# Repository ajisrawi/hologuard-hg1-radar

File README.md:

# HoloGuard HG-1: Ku-band GaN 4D holographic counter-UAS radar

A staring (holographic) 6 TX × 48 RX MIMO radar in the **same 163 × 203 × 57 mm envelope as the Echodyne EchoGuard**. It's lighter (1.06 kg vs 1.25 kg), uses less power (46.8 W vs 50 W), has longer range (Phantom 4: 1.5 km detect / 2.3 km spotlight track vs > 1 km) and better 3D accuracy (0.2° / 0.35° at 1 km vs 1° / 1.5°). Every beam is formed digitally from a 288-element virtual array, every CPI.

| Step | Documents | Sources / outputs |
|---|---|---|
| 1. High-level design | [docs/01_System_Design.md](docs/01_System_Design.md) | `hg1_params.py` (single source of truth), `analysis/` (link budget, trade study, figures) |
| 2. Board design + schematics | [docs/03_Board_Design.md](docs/03_Board_Design.md), [docs/05_Schematics.md](docs/05_Schematics.md) | `board/schematic/generate_schematics.py` → `board/kicad/*.kicad_sch` (ERC 0/0, parity clean); `board/generate_boards.py` → `*.kicad_pcb` (0 DRC errors), renders, `BOM_HG1.csv` |
| 3. Antenna design | [docs/02_Antenna.md](docs/02_Antenna.md), [docs/06_EM_Simulation.md](docs/06_EM_Simulation.md) | `antenna/array_design.py` → element CSV/JSON, beam patterns; `antenna/em/` → full-wave FEM (EMerge) of the element, scan-optimised on Modal |
| 4. Enclosure (FreeCAD) | [docs/04_Mechanical.md](docs/04_Mechanical.md) | `mech/build_enclosure.py` → `mech/out/HG1_enclosure.FCStd / .step / *.stl` |
| 5. Render (Blender) | [docs/04_Mechanical.md](docs/04_Mechanical.md) | `mech/render_blender.py` → `render/*.png`, `HG1_scene.blend` |
| 6. Firmware | [firmware/README.md](firmware/README.md) | Versal DSP chain + tracker (C++), STM32 housekeeping (C), simulator + verification |

## Regenerate everything

```bash
python analysis/system_budget.py
```

```bash
python antenna/array_design.py
```

```bash
"C:/Program Files/KiCad/10.0/bin/python.exe" board/generate_boards.py
```

```bash
sh board/render_boards.sh
```

```bash
"C:/Program Files/FreeCAD 1.1/bin/freecadcmd.exe" mech/build_enclosure.py
```

```bash
"C:/Program Files/Blender Foundation/Blender 5.2/blender.exe" -b --factory-startup -P mech/render_blender.py
```

```bash
cmd //c firmware\\build_host.bat
```

```bash
python firmware/sim/gen_scenario.py && firmware/build/hg1_radard.exe --input firmware/sim/out/scenario.iq --out firmware/sim/out && python firmware/sim/verify.py
```

## Honest status

This is a complete **design-stage** package:

- **Computed:** link budget, array and patterns.
- **Full-wave simulated:**
  - The radiating element has been simulated and optimised in an infinite-array FEM model to 60° azimuth / 40° elevation scan.
  - Its active |S11| is below −10 dB over 0.52–0.70 GHz around 16 GHz at every scan angle; see docs/06.
- **Schematics:** complete for all three boards, with ERC 0/0 and schematic↔PCB parity clean.
- **DRC-clean but unfinished:** board layouts are placed and RF-routed; the remaining digital/power routing is still to do.
- **Modelled:** enclosure and renders.
- **Verified in simulation:** the firmware, against independently synthesised raw ADC data.

Before hardware, it still needs:

- a finite-array and radome EM check, plus an independent-solver cross-check;
- the custom HRX-8 receiver RFIC (or a COTS brassboard);
- confirmation of Ku GaN PA availability;
- thermal CFD;
- the AIE/PL kernel implementation on the Versal.

Open risks are listed in docs/01 §10.

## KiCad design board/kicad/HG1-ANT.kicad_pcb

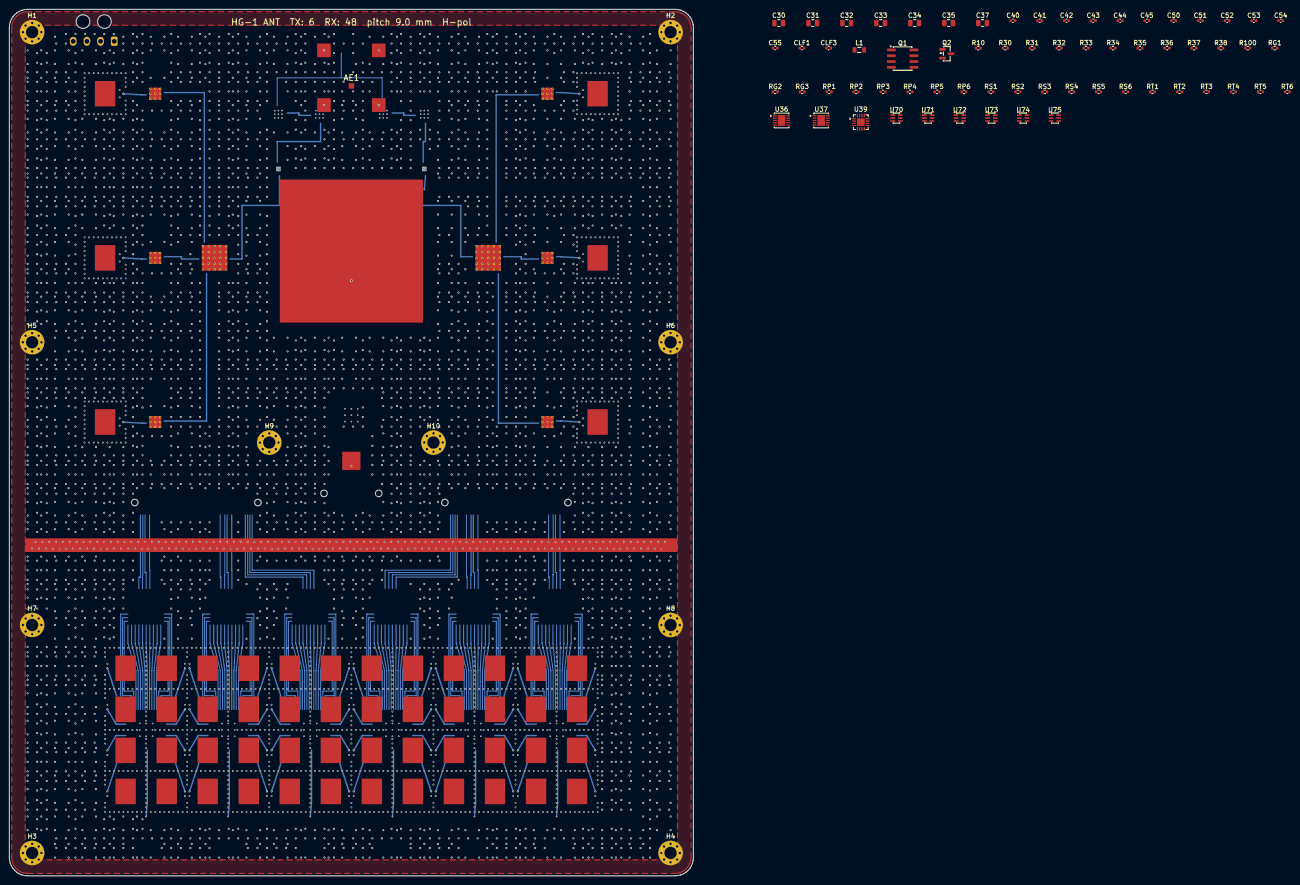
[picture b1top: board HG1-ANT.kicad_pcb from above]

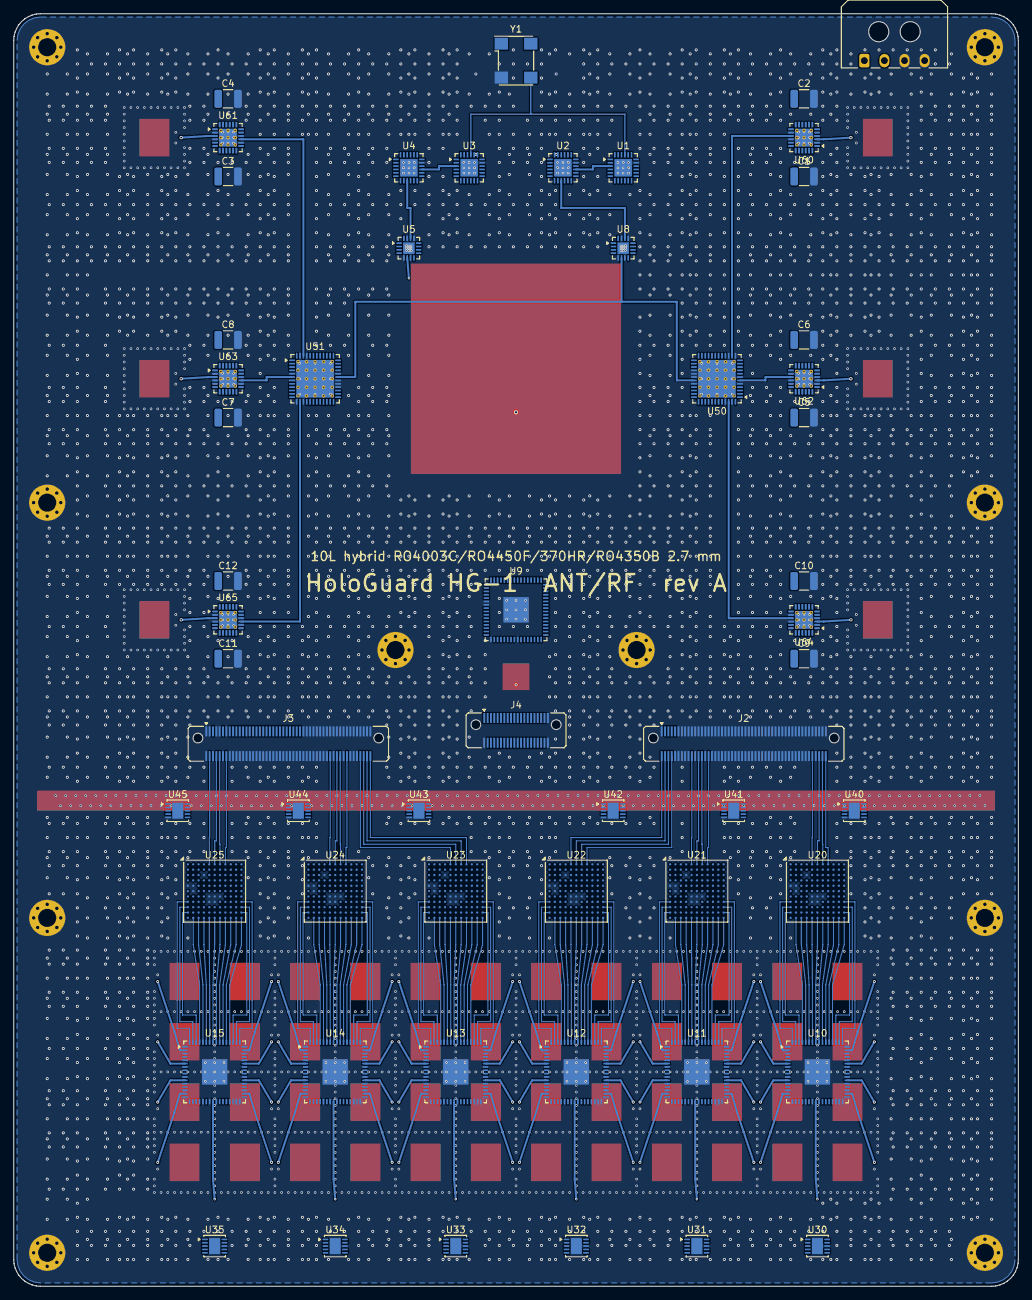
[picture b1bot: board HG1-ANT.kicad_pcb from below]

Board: 10 copper layers, 150.0 x 190.0 mm, 132 parts (56 on the bottom side), 251 nets.

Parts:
AE1: GNSS L1/L5 patch; GNSS_PATCH_18x18
C1, C2, C3, C4, C5, C6, C7, C8, C9, C10, C11, C12: 10u 50V; C_1210_3225Metric
C30, C31, C32, C33, C34, C35: 10u; C_0805_2012Metric
C37: 47u; C_0805_2012Metric
C40, C41, C42, C43, C44, C45: 1u; C_0402_1005Metric
C50, C51, C52, C53, C54, C55: 100n; C_0402_1005Metric
CLF1, CLF3: 2.2n C0G loop filter; C_0402_1005Metric
H1, H2, H3, H4, H5, H6, H7, H8, H9, H10: M2.5; MountingHole_2.7mm_M2.5_Pad_Via
J1: Micro-Fit 4p power in; Molex_Micro-Fit_3.0_43650-0400_1x04_P3.00mm_Horizontal
J2, J3: LSHM-150 JESD mezzanine; Samtec_LSHM-150-xx.x-x-DV-N_2x50_P0.50mm_Vertical
J4: LSHM-120 control mezzanine; Samtec_LSHM-120-xx.x-x-DV-N_2x20_P0.50mm_Vertical
L1: 1u; L_0805_2012Metric
Q1: P-MOSFET -60 V drain switch; SOIC-8_3.9x4.9mm_P1.27mm
Q2: 2N7002; SOT-23
R10, R100: 5.1k; R_0402_1005Metric
R30, R31, R32, R33, R34, R35, R36: 33.2k 0.1%; R_0402_1005Metric
R37: 20k; R_0402_1005Metric
R38: 80.6k; R_0402_1005Metric
RG1, RG2: 10k; R_0402_1005Metric
RG3: 100k; R_0402_1005Metric
RP1, RP2, RP3, RP4, RP5, RP6: 10k 0.1%; R_0402_1005Metric
RS1, RS2, RS3, RS4, RS5, RS6: 10m 1% 0805; R_0402_1005Metric
RT1, RT2, RT3, RT4, RT5, RT6: 10k B3435; R_0402_1005Metric
U1, U3: ADF4159; QFN-24-1EP_4x4mm_P0.5mm_EP2.6x2.6mm
U2, U4: HMC733LC4B; QFN-24-1EP_4x4mm_P0.5mm_EP2.6x2.6mm
U5, U8: HMC903LP3E; QFN-16-1EP_3x3mm_P0.5mm_EP1.7x1.7mm
U9: HMC7044; QFN-64-1EP_9x9mm_P0.5mm_EP3.8x3.8mm
U10, U11, U12, U13, U14, U15: HRX-8; QFN-64-1EP_9x9mm_P0.5mm_EP3.8x3.8mm
U20, U21, U22, U23, U24, U25: AD9083BBCZ; BGA-121_9.0x9.0mm_Layout11x11_P0.8mm_Ball0.4mm_Pad0.35mm_NS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
U30, U31, U32, U33, U34, U35: LT3045 3.3 V; DFN-10-1EP_3x3mm_P0.5mm_EP1.65x2.38mm
U36: LT3045 3.3 V (RF); DFN-10-1EP_3x3mm_P0.5mm_EP1.65x2.38mm
U37: TPS62913 1.0 V; DFN-10-1EP_3x3mm_P0.5mm_EP1.65x2.38mm
U39: ADS7138; QFN-16-1EP_3x3mm_P0.5mm_EP1.7x1.7mm
U40, U41, U42, U43, U44, U45: ADP7159 1.8 V; DFN-10-1EP_3x3mm_P0.5mm_EP1.65x2.38mm
U50, U51: ADAR1000; QFN-48-1EP_7x7mm_P0.5mm_EP5.6x5.6mm_ThermalVias
U60, U61, U62, U63, U64, U65: GaN PA 1 W; QFN-24-1EP_4x4mm_P0.5mm_EP2.65x2.65mm_ThermalVias
U70, U71, U72, U73, U74, U75: INA186A3; SOT-363_SC-70-6
Y1: 100 MHz OCXO; Oscillator_SMD_Diodes_FN-4Pin_7.0x5.0mm

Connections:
+1V0_ADC: C37.1, L1.2, R37.1, U20.E5, U20.E6, U20.E7, U21.E5, U21.E6, U21.E7, U22.E5, U22.E6, U22.E7, U23.E5, U23.E6, U23.E7, U24.E5, U24.E6, U24.E7, U25.E5, U25.E6, U25.E7
+3V3_RF: RP1.1, RP2.1, RP3.1, RP4.1, RP5.1, RP6.1, U1.5, U1.6, U1.7, U1.8, U1.16, U3.5, U3.6, U3.7, U3.8, U3.16, U5.3, U8.3, U9.10, U9.11, U9.12, U9.13, U36.9, U36.10, U39.14, U40.1, U40.2, U40.3, U41.1, U41.2, U41.3, U42.1, U42.2, U42.3, U43.1, U43.2, U43.3, U44.1, U44.2, U44.3, U45.1, U45.2, U45.3, U50.10, U50.11, U50.21, U51.10, U51.11, U51.21, U70.1, U71.1, U72.1, U73.1, U74.1, U75.1, Y1.1, Y1.4
+5V: J1.2, U2.3, U2.4, U4.3, U4.4, U30.1, U30.2, U30.3, U31.1, U31.2, U31.3, U32.1, U32.2, U32.3, U33.1, U33.2, U33.3, U34.1, U34.2, U34.3, U35.1, U35.2, U35.3, U36.1, U36.2, U36.3, U37.1, U37.2, U37.3
+28V_PA: J1.1, Q1.1, Q1.2, Q1.3, RG1.1
+28V_SW: Q1.5, Q1.6, Q1.7, Q1.8, RS1.1, RS2.1, RS3.1, RS4.1, RS5.1, RS6.1, U70.4, U71.4, U72.4, U73.4, U74.4, U75.4
-5V_BIAS: J4.37, U50.1, U51.1
ADC_CLK1: U9.30, U20.A2
ADC_CLK2: U9.32, U21.A2
ADC_CLK3: U9.34, U22.A2
ADC_CLK4: U9.36, U23.A2
ADC_CLK5: U9.38, U24.A2
ADC_CLK6: U9.40, U25.A2
ADC_SYSREF1: U9.31, U20.A10
ADC_SYSREF2: U9.33, U21.A10
ADC_SYSREF3: U9.35, U22.A10
ADC_SYSREF4: U9.37, U23.A10
ADC_SYSREF5: U9.39, U24.A10
ADC_SYSREF6: U9.41, U25.A10
AVDD1P8_1: U20.F5, U20.F6, U20.F7, U40.9, U40.10
AVDD1P8_2: U21.F5, U21.F6, U21.F7, U41.9, U41.10
AVDD1P8_3: U22.F5, U22.F6, U22.F7, U42.9, U42.10
AVDD1P8_4: U23.F5, U23.F6, U23.F7, U43.9, U43.10
AVDD1P8_5: U24.F5, U24.F6, U24.F7, U44.9, U44.10
AVDD1P8_6: U25.F5, U25.F6, U25.F7, U45.9, U45.10
CAL_PROBE: J2.3, J2.5, J2.7, J2.9
CHIRP_TRIG: J4.19, U1.12, U3.12
CS_ADC0: J4.10, U20.C3
CS_ADC1: J4.11, U21.C3
CS_ADC2: J4.12, U22.C3
CS_ADC3: J4.13, U23.C3
CS_ADC4: J4.14, U24.C3
CS_ADC5: J4.15, U25.C3
CS_BF0: J4.28, U50.27
CS_BF1: J4.29, U51.27
CS_CLK: J4.18, U9.4
CS_PLL_LO: J4.17, U3.15
CS_PLL_TX: J4.16, U1.15
CS_RFIC0: J4.4, U10.19
CS_RFIC1: J4.5, U11.19
CS_RFIC2: J4.6, U12.19
CS_RFIC3: J4.7, U13.19
CS_RFIC4: J4.8, U14.19
CS_RFIC5: J4.9, U15.19
DRAIN_GATE: Q1.4, RG1.2, RG2.1
DRAIN_PD: Q2.3, RG2.2
EN_DRAIN_SW: J4.32, Q2.1, RG3.1
FB_1V0: R37.2, R38.1, U37.4
FPGA_REFCLK: J4.23, U9.42
FPGA_SYSREF: J4.24, U9.43
GND: AE1.2, AE1.3, AE1.4, AE1.5, C1.2, C2.2, C3.2, C4.2, C5.2, C6.2, C7.2, C8.2, C9.2, C10.2, C11.2, C12.2, C30.2, C31.2, C32.2, C33.2, C34.2, C35.2, C37.2, C40.2, C41.2, C42.2, C43.2, C44.2, C45.2, C50.2, C51.2, C52.2, C53.2, C54.2, C55.2, CLF1.2, CLF3.2, H1.1, H2.1, H3.1, H4.1, H5.1, H6.1, H7.1, H8.1, H9.1, H10.1, J1.3, J1.4, J2.1, J2.10, J2.11, J2.12, J2.13, J2.14, J2.15, J2.16, J2.17, J2.18, J2.19, J2.21, J2.22, J2.23, J2.25, J2.27, J2.28, J2.29, J2.31, J2.32, J2.33, J2.34, J2.35, J2.36, J2.37, J2.38, J2.39, J2.40, J2.41, J2.42, J2.43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
GNSS_RF: AE1.1, J4.35
I2C3_SCL: J4.33, U39.9
I2C3_SDA: J4.34, U39.10
ID_PA1: J3.5, J3.23, J3.35, J3.47, U70.6
ID_PA2: J3.11, J3.25, J3.37, J3.49, U71.6
ID_PA3: J3.15, J3.27, J3.39, J3.51, U72.6
ID_PA4: J3.17, J3.29, J3.41, J3.53, U73.6
ID_PA5: J3.19, J3.31, J3.43, J3.55, U74.6
ID_PA6: J3.21, J3.33, J3.45, J3.57, U75.6
IF1_CH1I: U10.49, U20.H11
IF1_CH1Q: U10.50, U20.J11
IF1_CH2I: U10.51, U20.K11
IF1_CH2Q: U10.52, U20.L11
IF1_CH3I: U10.53, U20.L10
IF1_CH3Q: U10.54, U20.L9
IF1_CH4I: U10.55, U20.L8
IF1_CH4Q: U10.56, U20.L7
IF1_CH5I: U10.57, U20.L6
IF1_CH5Q: U10.58, U20.L5
IF1_CH6I: U10.59, U20.L4
IF1_CH6Q: U10.60, U20.L3
IF1_CH7I: U10.61, U20.L2
IF1_CH7Q: U10.62, U20.K1
IF1_CH8I: U10.63, U20.J1
IF1_CH8Q: U10.64, U20.H1
IF2_CH1I: U11.49, U21.H11
IF2_CH1Q: U11.50, U21.J11
IF2_CH2I: U11.51, U21.K11
IF2_CH2Q: U11.52, U21.L11
IF2_CH3I: U11.53, U21.L10
IF2_CH3Q: U11.54, U21.L9
IF2_CH4I: U11.55, U21.L8
IF2_CH4Q: U11.56, U21.L7
IF2_CH5I: U11.57, U21.L6
IF2_CH5Q: U11.58, U21.L5
IF2_CH6I: U11.59, U21.L4
IF2_CH6Q: U11.60, U21.L3
IF2_CH7I: U11.61, U21.L2
IF2_CH7Q: U11.62, U21.K1
IF2_CH8I: U11.63, U21.J1
IF2_CH8Q: U11.64, U21.H1
IF3_CH1I: U12.49, U22.H11
IF3_CH1Q: U12.50, U22.J11
IF3_CH2I: U12.51, U22.K11
IF3_CH2Q: U12.52, U22.L11
IF3_CH3I: U12.53, U22.L10
IF3_CH3Q: U12.54, U22.L9
IF3_CH4I: U12.55, U22.L8
IF3_CH4Q: U12.56, U22.L7
IF3_CH5I: U12.57, U22.L6
IF3_CH5Q: U12.58, U22.L5
IF3_CH6I: U12.59, U22.L4
IF3_CH6Q: U12.60, U22.L3
IF3_CH7I: U12.61, U22.L2
IF3_CH7Q: U12.62, U22.K1
IF3_CH8I: U12.63, U22.J1
IF3_CH8Q: U12.64, U22.H1
IF4_CH1I: U13.49, U23.H11
IF4_CH1Q: U13.50, U23.J11
IF4_CH2I: U13.51, U23.K11
IF4_CH2Q: U13.52, U23.L11
IF4_CH3I: U13.53, U23.L10
IF4_CH3Q: U13.54, U23.L9
IF4_CH4I: U13.55, U23.L8
IF4_CH4Q: U13.56, U23.L7
IF4_CH5I: U13.57, U23.L6
IF4_CH5Q: U13.58, U23.L5
IF4_CH6I: U13.59, U23.L4
IF4_CH6Q: U13.60, U23.L3
IF4_CH7I: U13.61, U23.L2
IF4_CH7Q: U13.62, U23.K1
IF4_CH8I: U13.63, U23.J1
IF4_CH8Q: U13.64, U23.H1
IF5_CH1I: U14.49, U24.H11
IF5_CH1Q: U14.50, U24.J11
IF5_CH2I: U14.51, U24.K11
IF5_CH2Q: U14.52, U24.L11
IF5_CH3I: U14.53, U24.L10
IF5_CH3Q: U14.54, U24.L9
IF5_CH4I: U14.55, U24.L8
IF5_CH4Q: U14.56, U24.L7
IF5_CH5I: U14.57, U24.L6
IF5_CH5Q: U14.58, U24.L5
IF5_CH6I: U14.59, U24.L4
IF5_CH6Q: U14.60, U24.L3
IF5_CH7I: U14.61, U24.L2
IF5_CH7Q: U14.62, U24.K1
IF5_CH8I: U14.63, U24.J1
IF5_CH8Q: U14.64, U24.H1
IF6_CH1I: U15.49, U25.H11
IF6_CH1Q: U15.50, U25.J11
IF6_CH2I: U15.51, U25.K11
IF6_CH2Q: U15.52, U25.L11
IF6_CH3I: U15.53, U25.L10
IF6_CH3Q: U15.54, U25.L9
IF6_CH4I: U15.55, U25.L8
IF6_CH4Q: U15.56, U25.L7
IF6_CH5I: U15.57, U25.L6
IF6_CH5Q: U15.58, U25.L5
IF6_CH6I: U15.59, U25.L4
IF6_CH6Q: U15.60, U25.L3
IF6_CH7I: U15.61, U25.L2
IF6_CH7Q: U15.62, U25.K1
IF6_CH8I: U15.63, U25.J1
IF6_CH8Q: U15.64, U25.H1
JESD1_L0: J2.100, U20.A8
JESD1_L1: J2.98, U20.A7
JESD1_L2: J2.96, U20.A6
JESD1_L3: J2.92, U20.A5
JESD2_L0: J2.30, U21.A8
JESD2_L1: J2.26, U21.A7
JESD2_L2: J2.24, U21.A6
JESD2_L3: J2.20, U21.A5
JESD3_L0: J2.8, U22.A8
JESD3_L1: J2.6, U22.A7
JESD3_L2: J2.4, U22.A6
JESD3_L3: J2.2, U22.A5
JESD4_L0: J3.100, U23.A8
JESD4_L1: J3.98, U23.A7
JESD4_L2: J3.96, U23.A6
JESD4_L3: J3.94, U23.A5
JESD5_L0: J3.86, U24.A8
JESD5_L1: J3.82, U24.A7
JESD5_L2: J3.80, U24.A6
JESD5_L3: J3.76, U24.A5
JESD6_L0: J3.14, U25.A8
JESD6_L1: J3.10, U25.A7
JESD6_L2: J3.8, U25.A6
JESD6_L3: J3.4, U25.A5
JESD_SYNC: J4.20, U20.B1, U21.B1, U22.B1, U23.B1, U24.B1, U25.B1
LO_CHIRP: U5.6, U10.24, U11.24, U12.24, U13.24, U14.24, U15.24
LO_VCO_DIV: U3.9, U4.21
LO_VCO_OUT: U4.9, U5.14
LO_VCO_TUNE: CLF3.1, U3.3, U4.15
MCU_SPI_MISO: J4.27, U50.26, U51.26
MCU_SPI_MOSI: J4.26, U50.25, U51.25
MCU_SPI_SCK: J4.25, U50.24, U51.24
NTC_PA1: RP1.2, RT1.1, U39.1
NTC_PA2: RP2.2, RT2.1, U39.2
NTC_PA3: RP3.2, RT3.1, U39.3
NTC_PA4: RP4.2, RT4.1, U39.4
NTC_PA5: RP5.2, RT5.1, U39.5
NTC_PA6: RP6.2, RT6.1, U39.6
PA_D1: C1.1, C2.1, RS1.2, U60.21, U60.22, U70.5
PA_D2: C3.1, C4.1, RS2.2, U61.21, U61.22, U71.5
PA_D3: C5.1, C6.1, RS3.2, U62.21, U62.22, U72.5
PA_D4: C7.1, C8.1, RS4.2, U63.21, U63.22, U73.5
PA_D5: C9.1, C10.1, RS5.2, U64.21, U64.22, U74.5
PA_D6: C11.1, C12.1, RS6.2, U65.21, U65.22, U75.5
PLL_LD_LO: J4.22, U3.18
PLL_LD_TX: J4.21, U1.18
REF_100M: U1.21, U3.21, U9.1, Y1.3
REF_ADC1: C40.1, U40.8
REF_ADC2: C41.1, U41.8
REF_ADC3: C42.1, U42.8
REF_ADC4: C43.1, U43.8
REF_ADC5: C44.1, U44.8
REF_ADC6: C45.1, U45.8
RF_RESET_N: J4.38, U10.20, U11.20, U12.20, U13.20, U14.20, U15.20
RSET_LO: R100.1, U3.20
RSET_TX: R10.1, U1.20
SET_RF: R36.1, U36.7
SET_RX1: R30.1, U30.7
SET_RX2: R31.1, U31.7
SET_RX3: R32.1, U32.7
SET_RX4: R33.1, U33.7
SET_RX5: R34.1, U34.7
SET_RX6: R35.1, U35.7
SPI_MOSI: J4.3, U1.14, U3.14, U9.5, U10.18, U11.18, U12.18, U13.18, U14.18, U15.18, U20.C2, U21.C2, U22.C2, U23.C2, U24.C2, U25.C2
SPI_SCLK: J4.1, U1.13, U3.13, U9.3, U10.17, U11.17, U12.17, U13.17, U14.17, U15.17, U20.C1, U21.C1, U22.C1, U23.C1, U24.C1, U25.C1
SW_1V0: L1.1, U37.9, U37.10
TXDRV1: U50.14, U60.15
TXDRV2: U51.46, U61.15
TXDRV3: U50.6, U62.15
TXDRV4: U51.6, U63.15
TXDRV5: U50.46, U64.15
TXDRV6: U51.14, U65.15
TX_CHIRP: U8.6, U50.31, U51.31
TX_LOAD: J4.31, U50.34, U51.34
TX_MUTE_N: J4.30, U50.33, U50.37, U51.33, U51.37
TX_VCO_DIV: U1.9, U2.21
TX_VCO_OUT: U2.9, U8.14
TX_VCO_TUNE: CLF1.1, U1.3, U2.15
VCC_RX1: C30.1, U10.4, U10.8, U10.9, U10.13, U10.26, U10.36, U10.40, U10.41, U10.45, U30.9, U30.10
VCC_RX2: C31.1, U11.4, U11.8, U11.9, U11.13, U11.26, U11.36, U11.40, U11.41, U11.45, U31.9, U31.10
VCC_RX3: C32.1, U12.4, U12.8, U12.9, U12.13, U12.26, U12.36, U12.40, U12.41, U12.45, U32.9, U32.10
VCC_RX4: C33.1, U13.4, U13.8, U13.9, U13.13, U13.26, U13.36, U13.40, U13.41, U13.45, U33.9, U33.10
VCC_RX5: C34.1, U14.4, U14.8, U14.9, U14.13, U14.26, U14.36, U14.40, U14.41, U14.45, U34.9, U34.10
VCC_RX6: C35.1, U15.4, U15.8, U15.9, U15.13, U15.26, U15.36, U15.40, U15.41, U15.45, U35.9, U35.10
VCM1: C50.1, U10.27, U20.D1
VCM2: C51.1, U11.27, U21.D1
VCM3: C52.1, U12.27, U22.D1
VCM4: C53.1, U13.27, U23.D1
VCM5: C54.1, U14.27, U24.D1
VCM6: C55.1, U15.27, U25.D1
VG_PA1: U50.20, U60.18
VG_PA2: U51.40, U61.18
VG_PA3: U50.2, U62.18
VG_PA4: U51.2, U63.18
VG_PA5: U50.40, U64.18
VG_PA6: U51.20, U65.18

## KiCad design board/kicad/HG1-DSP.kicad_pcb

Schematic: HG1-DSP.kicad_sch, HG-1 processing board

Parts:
C4, C101: 1u; C_0402_1005Metric
C7, C100: 100n; C_0402_1005Metric
C12: 220n; C_0402_1005Metric
C23, C24: 22u; C_0805_2012Metric
C102: 47u; C_0805_2012Metric
CL1, CL2: 470u polymer; C_0805_2012Metric
CR25, CR26, CR27, CR28, CR29: 1u; C_0402_1005Metric
H1, H2, H3, H4, H5, H6: M2.5; MountingHole_2.7mm_M2.5_Pad_Via
J2, J3: LSHM-150 (mate ANT); Samtec_LSHM-150-xx.x-x-DV-N_2x50_P0.50mm_Vertical
J4: LSHM-120 (mate ANT); Samtec_LSHM-120-xx.x-x-DV-N_2x20_P0.50mm_Vertical
J5: FFC to PWR/IO; Hirose_FH12-30S-0.5SH_1x30-1MP_P0.50mm_Horizontal
J6: Micro-Fit +12V in; Molex_Micro-Fit_3.0_43650-0400_1x04_P3.00mm_Horizontal
J7: JTAG; PinHeader_1x06_P1.27mm_Vertical
J8: SWD (Tag-Connect TC2030); PinHeader_1x05_P1.27mm_Vertical
J9: U.FL OTA-cal port; U.FL_Hirose_U.FL-R-SMT-1_Vertical
L1, L2: XAL6030 0.22u; L_Coilcraft_XAL6030-XXX
L3: XAL6030 1.0u; L_Coilcraft_XAL6030-XXX
L23, L24: 2.2u; L_0805_2012Metric
R100: 1M; R_0402_1005Metric
R101: 316k; R_0402_1005Metric
R102: 18.2k; R_0402_1005Metric
R103, R105: 100k; R_0402_1005Metric
R104, R106: 49.9k; R_0402_1005Metric
RD1, RD2: 10k; R_0402_1005Metric
RIO100: 0R (3.3 V to PWR/IO board); R_0402_1005Metric
RN1: 20k 0.1%; R_0402_1005Metric
RN2: 40.2k 0.1%; R_0402_1005Metric
RP1, RP2: 10k 0.1%; R_0402_1005Metric
RPG100: 10k; R_0402_1005Metric
RPOR100: 4.7k; R_0402_1005Metric
RT1, RT2: 10k B3435; R_0402_1005Metric
U1: XCVE2302-1LSESFVA784; Microchip_FCVG784_BGA-784_23x23mm_Layout28x28_P0.8mm
U2, U3: MT53E1G32D2 LPDDR4; BGA-200_10x14.5mm_Layout12x22_P0.8x0.65mm
U4: eMMC 64 GB pSLC; LFBGA-153_11.5x13mm_Layout14x14_P0.5mm
U5: MT25QU512 QSPI; WSON-8-1EP_8x6mm_P1.27mm_EP3.4x4.3mm
U6: DP83867IRRGZ; QFN-48-1EP_7x7mm_P0.5mm_EP5.6x5.6mm
U7: STM32G474RET6; LQFP-64_10x10mm_P0.5mm
U8: NEO-F10T (NEO footprint); ublox_NEO
U9: MDBT50Q nRF52840; Raytac_MDBT50Q
U10: nRF7002; QFN-40-1EP_6x6mm_P0.5mm_EP4.6x4.6mm
U11: ISM330DHCX; Bosch_LGA-14_3x2.5mm_P0.5mm
U12: LIS2MDL; LGA-12_2x2mm_P0.5mm
U20, U21: TPS546D24A 0.8 V; QFN-40-1EP_6x6mm_P0.5mm_EP4.6x4.6mm_ThermalVias
U22: LT8640S 3.3 V; QFN-24-1EP_4x4mm_P0.5mm_EP2.6x2.6mm
U23: TPS62913 1.8 V; DFN-10-1EP_3x3mm_P0.5mm_EP1.65x2.38mm
U24: TPS62913 1.1 V; DFN-10-1EP_3x3mm_P0.5mm_EP1.65x2.38mm
U25: ADP7159 1.5 V LDO; DFN-10-1EP_3x3mm_P0.5mm_EP1.65x2.38mm
U26: ADP7159 0.88 V LDO; DFN-10-1EP_3x3mm_P0.5mm_EP1.65x2.38mm
U27: ADP7159 1.2 V LDO; DFN-10-1EP_3x3mm_P0.5mm_EP1.65x2.38mm
U28: ADP7159 2.5 V LDO; DFN-10-1EP_3x3mm_P0.5mm_EP1.65x2.38mm
U29: ADP7159 1.0 V LDO; DFN-10-1EP_3x3mm_P0.5mm_EP1.65x2.38mm
U30: TPS3700 -5 V window; SOT-23-6
Y2: 33.333 MHz XO (PS_REFCLK); Oscillator_SMD_EuroQuartz_XO53-4Pin_5.0x3.2mm
Y3: 25 MHz XO; Oscillator_SMD_EuroQuartz_XO53-4Pin_5.0x3.2mm

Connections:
+0V88_GT: U1.AH8 (GTYP_AVCC), U26.9 (VOUT), U26.10 (VOUT)
+1V0_PHY: U6.32 (VDD1P0), U6.33 (VDD1P0), U29.9 (VOUT), U29.10 (VOUT)
+1V1_DDR: C24.1, L24.2, R105.1, U1.AH5 (VCCO_DDR), U2.D10 (VDD2), U2.D11 (VDD2), U2.D12 (VDDQ), U2.E1 (VDDQ), U3.D10 (VDD2), U3.D11 (VDD2), U3.D12 (VDDQ), U3.E1 (VDDQ)
+1V2_GT: U1.AH9 (GTYP_AVTT), U27.9 (VOUT), U27.10 (VOUT)
+1V5_AUX: U1.AH4 (VCCAUX), U25.9 (VOUT), U25.10 (VOUT)
+1V8: C23.1, J7.1, L23.2, R103.1, U1.AH6 (VCCO_1V8), U2.D8 (VDD1), U2.D9 (VDD1), U3.D8 (VDD1), U3.D9 (VDD1), U4.A14 (VCCQ), U4.B1 (VCCQ), U5.8 (VCC), U6.34 (VDDIO), U6.35 (VDDIO), U10.12 (VDDIO), U11.5 (VDDIO), U11.8 (VDD), U12.9 (Vdd), U12.10 (Vdd_IO), U26.1 (VIN), U26.2 (VIN), U26.3 (EN), U27.1 (VIN), U27.2 (VIN), U27.3 (EN), U29.1 (VIN), U29.2 (VIN), U29.3 (EN), Y2.1 (EN), Y2.4 (VCC), Y3.1 (EN), Y3.4 (VCC)
+2V5: U6.30 (VDDA2P5), U6.31 (VDDA2P5), U28.9 (VOUT), U28.10 (VOUT)
+3V3: C102.1, J8.1, L3.2, R100.1, RD1.1, RIO100.1, RN1.1, RP1.1, RP2.1, RPG100.1, RPOR100.1, U1.AH7 (VCCO_3V3), U4.A12 (VCC), U4.A13 (VCC), U7.1 (VBAT), U7.16 (VDD), U7.28 (VREF+), U7.29 (VDDA), U7.32 (VDD), U7.48 (VDD), U7.64 (VDD), U8.22 (V_BCKP), U8.23 (VCC), U9.28 (VDD), U9.30 (VDDH), U10.10 (VBAT), U10.11 (VBAT), U25.1 (VIN), U25.2 (VIN), U25.3 (EN), U28.1 (VIN), U28.2 (VIN), U28.3 (EN), U30.5 (VDD)
+3V3_IO: J5.27, RIO100.2
+12V: J6.1, J6.2, U20.1 (VIN), U20.2 (VIN), U20.3 (VIN), U21.1 (VIN), U21.2 (VIN), U21.3 (VIN), U22.1 (VIN), U22.2 (VIN), U23.1 (VIN), U23.2 (VIN), U24.1 (VIN), U24.2 (VIN)
-5V_BIAS: J4.37, J5.25, J5.26, RN2.2
BLE_RX: U1.AG11 (BLE_RX), U9.24 (P0.08)
BLE_TX: U1.AG10 (BLE_TX), U9.22 (P0.06)
BST_3V3: C100.1, U22.13 (BST)
CAL_PROBE: J2.3, J2.5, J2.7, J2.9, J9.1 (In)
CHIRP_TRIG: J4.19, U1.AA18 (CHIRP_TRIG)
CS_ADC0: J4.10, U1.AA9 (CS_ADC0)
CS_ADC1: J4.11, U1.AA10 (CS_ADC1)
CS_ADC2: J4.12, U1.AA11 (CS_ADC2)
CS_ADC3: J4.13, U1.AA12 (CS_ADC3)
CS_ADC4: J4.14, U1.AA13 (CS_ADC4)
CS_ADC5: J4.15, U1.AA14 (CS_ADC5)
CS_BF0: J4.28, U7.18 (PA4)
CS_BF1: J4.29, U7.51 (PA15)
CS_CLK: J4.18, U1.AA17 (CS_CLK)
CS_PLL_LO: J4.17, U1.AA16 (CS_PLL_LO)
CS_PLL_TX: J4.16, U1.AA15 (CS_PLL_TX)
CS_RFIC0: J4.4, U1.AA3 (CS_RFIC0)
CS_RFIC1: J4.5, U1.AA4 (CS_RFIC1)
CS_RFIC2: J4.6, U1.AA5 (CS_RFIC2)
CS_RFIC3: J4.7, U1.AA6 (CS_RFIC3)
CS_RFIC4: J4.8, U1.AA7 (CS_RFIC4)
CS_RFIC5: J4.9, U1.AA8 (CS_RFIC5)
DDRA_CA0: U1.AA22 (DDRA_CA0), U2.A1 (CA0)
DDRA_CA1: U1.AA23 (DDRA_CA1), U2.A2 (CA1)
DDRA_CA2: U1.AA24 (DDRA_CA2), U2.A3 (CA2)
DDRA_CA3: U1.AA25 (DDRA_CA3), U2.A4 (CA3)
DDRA_CA4: U1.AA26 (DDRA_CA4), U2.A5 (CA4)
DDRA_CA5: U1.AA27 (DDRA_CA5), U2.A8 (CA5)
DDRA_CKE: U1.AB1 (DDRA_CKE), U2.A10 (CKE)
DDRA_CK_C: U1.AB3 (DDRA_CK_C), U2.A12 (CK_C)
DDRA_CK_T: U1.AB2 (DDRA_CK_T), U2.A11 (CK_T)
DDRA_CS: U1.AA28 (DDRA_CS), U2.A9 (CS)
DDRA_DMI0: U1.AC17 (DDRA_DMI0), U2.D2 (DMI0)
DDRA_DMI1: U1.AC18 (DDRA_DMI1), U2.D3 (DMI1)
DDRA_DMI2: U1.AC19 (DDRA_DMI2), U2.D4 (DMI2)
DDRA_DMI3: U1.AC20 (DDRA_DMI3), U2.D5 (DMI3)
DDRA_DQ0: U1.AB5 (DDRA_DQ0), U2.AA2 (DQ0)
DDRA_DQ1: U1.AB6 (DDRA_DQ1), U2.AA3 (DQ1)
DDRA_DQ2: U1.AB7 (DDRA_DQ2), U2.AA4 (DQ2)
DDRA_DQ3: U1.AB8 (DDRA_DQ3), U2.AA5 (DQ3)
DDRA_DQ4: U1.AB9 (DDRA_DQ4), U2.AA8 (DQ4)
DDRA_DQ5: U1.AB10 (DDRA_DQ5), U2.AA9 (DQ5)
DDRA_DQ6: U1.AB11 (DDRA_DQ6), U2.AA10 (DQ6)
DDRA_DQ7: U1.AB12 (DDRA_DQ7), U2.AA11 (DQ7)
DDRA_DQ8: U1.AB13 (DDRA_DQ8), U2.AA12 (DQ8)
DDRA_DQ9: U1.AB14 (DDRA_DQ9), U2.AB1 (DQ9)
DDRA_DQ10: U1.AB15 (DDRA_DQ10), U2.AB2 (DQ10)
DDRA_DQ11: U1.AB16 (DDRA_DQ11), U2.AB3 (DQ11)
DDRA_DQ12: U1.AB17 (DDRA_DQ12), U2.AB4 (DQ12)
DDRA_DQ13: U1.AB18 (DDRA_DQ13), U2.AB5 (DQ13)
DDRA_DQ14: U1.AB19 (DDRA_DQ14), U2.AB8 (DQ14)
DDRA_DQ15: U1.AB20 (DDRA_DQ15), U2.AB9 (DQ15)
DDRA_DQ16: U1.AB21 (DDRA_DQ16), U2.AB10 (DQ16)
DDRA_DQ17: U1.AB22 (DDRA_DQ17), U2.AB11 (DQ17)
DDRA_DQ18: U1.AB23 (DDRA_DQ18), U2.AB12 (DQ18)
DDRA_DQ19: U1.AB24 (DDRA_DQ19), U2.B1 (DQ19)
DDRA_DQ20: U1.AB25 (DDRA_DQ20), U2.B2 (DQ20)
DDRA_DQ21: U1.AB26 (DDRA_DQ21), U2.B3 (DQ21)
DDRA_DQ22: U1.AB27 (DDRA_DQ22), U2.B4 (DQ22)
DDRA_DQ23: U1.AB28 (DDRA_DQ23), U2.B5 (DQ23)
DDRA_DQ24: U1.AC1 (DDRA_DQ24), U2.B8 (DQ24)
DDRA_DQ25: U1.AC2 (DDRA_DQ25), U2.B9 (DQ25)
DDRA_DQ26: U1.AC3 (DDRA_DQ26), U2.B10 (DQ26)
DDRA_DQ27: U1.AC4 (DDRA_DQ27), U2.B11 (DQ27)
DDRA_DQ28: U1.AC5 (DDRA_DQ28), U2.B12 (DQ28)
DDRA_DQ29: U1.AC6 (DDRA_DQ29), U2.C1 (DQ29)
DDRA_DQ30: U1.AC7 (DDRA_DQ30), U2.C2 (DQ30)
DDRA_DQ31: U1.AC8 (DDRA_DQ31), U2.C3 (DQ31)
DDRA_DQS_C0: U1.AC13 (DDRA_DQS_C0), U2.C10 (DQS_C0)
DDRA_DQS_C1: U1.AC14 (DDRA_DQS_C1), U2.C11 (DQS_C1)
DDRA_DQS_C2: U1.AC15 (DDRA_DQS_C2), U2.C12 (DQS_C2)
DDRA_DQS_C3: U1.AC16 (DDRA_DQS_C3), U2.D1 (DQS_C3)
DDRA_DQS_T0: U1.AC9 (DDRA_DQS_T0), U2.C4 (DQS_T0)
DDRA_DQS_T1: U1.AC10 (DDRA_DQS_T1), U2.C5 (DQS_T1)
DDRA_DQS_T2: U1.AC11 (DDRA_DQS_T2), U2.C8 (DQS_T2)
DDRA_DQS_T3: U1.AC12 (DDRA_DQS_T3), U2.C9 (DQS_T3)
DDRA_RESET_N: U1.AB4 (DDRA_RESET_N), U2.AA1 (RESET_N)
DDRB_CA0: U1.AC21 (DDRB_CA0), U3.A1 (CA0)
DDRB_CA1: U1.AC22 (DDRB_CA1), U3.A2 (CA1)
DDRB_CA2: U1.AC23 (DDRB_CA2), U3.A3 (CA2)
DDRB_CA3: U1.AC24 (DDRB_CA3), U3.A4 (CA3)
DDRB_CA4: U1.AC25 (DDRB_CA4), U3.A5 (CA4)
DDRB_CA5: U1.AC26 (DDRB_CA5), U3.A8 (CA5)
DDRB_CKE: U1.AC28 (DDRB_CKE), U3.A10 (CKE)
DDRB_CK_C: U1.AD2 (DDRB_CK_C), U3.A12 (CK_C)
DDRB_CK_T: U1.AD1 (DDRB_CK_T), U3.A11 (CK_T)
DDRB_CS: U1.AC27 (DDRB_CS), U3.A9 (CS)
DDRB_DMI0: U1.AE16 (DDRB_DMI0), U3.D2 (DMI0)
DDRB_DMI1: U1.AE17 (DDRB_DMI1), U3.D3 (DMI1)
DDRB_DMI2: U1.AE18 (DDRB_DMI2), U3.D4 (DMI2)
DDRB_DMI3: U1.AE19 (DDRB_DMI3), U3.D5 (DMI3)
DDRB_DQ0: U1.AD4 (DDRB_DQ0), U3.AA2 (DQ0)
DDRB_DQ1: U1.AD5 (DDRB_DQ1), U3.AA3 (DQ1)
DDRB_DQ2: U1.AD6 (DDRB_DQ2), U3.AA4 (DQ2)
DDRB_DQ3: U1.AD7 (DDRB_DQ3), U3.AA5 (DQ3)
DDRB_DQ4: U1.AD8 (DDRB_DQ4), U3.AA8 (DQ4)
DDRB_DQ5: U1.AD9 (DDRB_DQ5), U3.AA9 (DQ5)
DDRB_DQ6: U1.AD10 (DDRB_DQ6), U3.AA10 (DQ6)
DDRB_DQ7: U1.AD11 (DDRB_DQ7), U3.AA11 (DQ7)
DDRB_DQ8: U1.AD12 (DDRB_DQ8), U3.AA12 (DQ8)
DDRB_DQ9: U1.AD13 (DDRB_DQ9), U3.AB1 (DQ9)
DDRB_DQ10: U1.AD14 (DDRB_DQ10), U3.AB2 (DQ10)
DDRB_DQ11: U1.AD15 (DDRB_DQ11), U3.AB3 (DQ11)
DDRB_DQ12: U1.AD16 (DDRB_DQ12), U3.AB4 (DQ12)
DDRB_DQ13: U1.AD17 (DDRB_DQ13), U3.AB5 (DQ13)
DDRB_DQ14: U1.AD18 (DDRB_DQ14), U3.AB8 (DQ14)
DDRB_DQ15: U1.AD19 (DDRB_DQ15), U3.AB9 (DQ15)
DDRB_DQ16: U1.AD20 (DDRB_DQ16), U3.AB10 (DQ16)
DDRB_DQ17: U1.AD21 (DDRB_DQ17), U3.AB11 (DQ17)
DDRB_DQ18: U1.AD22 (DDRB_DQ18), U3.AB12 (DQ18)
DDRB_DQ19: U1.AD23 (DDRB_DQ19), U3.B1 (DQ19)
DDRB_DQ20: U1.AD24 (DDRB_DQ20), U3.B2 (DQ20)
DDRB_DQ21: U1.AD25 (DDRB_DQ21), U3.B3 (DQ21)
DDRB_DQ22: U1.AD26 (DDRB_DQ22), U3.B4 (DQ22)
DDRB_DQ23: U1.AD27 (DDRB_DQ23), U3.B5 (DQ23)
DDRB_DQ24: U1.AD28 (DDRB_DQ24), U3.B8 (DQ24)
DDRB_DQ25: U1.AE1 (DDRB_DQ25), U3.B9 (DQ25)
DDRB_DQ26: U1.AE2 (DDRB_DQ26), U3.B10 (DQ26)
DDRB_DQ27: U1.AE3 (DDRB_DQ27), U3.B11 (DQ27)
DDRB_DQ28: U1.AE4 (DDRB_DQ28), U3.B12 (DQ28)
DDRB_DQ29: U1.AE5 (DDRB_DQ29), U3.C1 (DQ29)
DDRB_DQ30: U1.AE6 (DDRB_DQ30), U3.C2 (DQ30)
DDRB_DQ31: U1.AE7 (DDRB_DQ31), U3.C3 (DQ31)
DDRB_DQS_C0: U1.AE12 (DDRB_DQS_C0), U3.C10 (DQS_C0)
DDRB_DQS_C1: U1.AE13 (DDRB_DQS_C1), U3.C11 (DQS_C1)
DDRB_DQS_C2: U1.AE14 (DDRB_DQS_C2), U3.C12 (DQS_C2)
DDRB_DQS_C3: U1.AE15 (DDRB_DQS_C3), U3.D1 (DQS_C3)
DDRB_DQS_T0: U1.AE8 (DDRB_DQS_T0), U3.C4 (DQS_T0)
DDRB_DQS_T1: U1.AE9 (DDRB_DQS_T1), U3.C5 (DQS_T1)
DDRB_DQS_T2: U1.AE10 (DDRB_DQS_T2), U3.C8 (DQS_T2)
DDRB_DQS_T3: U1.AE11 (DDRB_DQS_T3), U3.C9 (DQS_T3)
DDRB_RESET_N: U1.AD3 (DDRB_RESET_N), U3.AA1 (RESET_N)
DISC_IN: J5.17, U1.AG22 (DISC_IN)
EMMC_CLK: U1.AE20 (EMMC_CLK), U4.A1 (CLK)
EMMC_CMD: U1.AE21 (EMMC_CMD), U4.A2 (CMD)
EMMC_D0: U1.AE22 (EMMC_D0), U4.A4 (DAT0)
EMMC_D1: U1.AE23 (EMMC_D1), U4.A5 (DAT1)
EMMC_D2: U1.AE24 (EMMC_D2), U4.A6 (DAT2)
EMMC_D3: U1.AE25 (EMMC_D3), U4.A7 (DAT3)
EMMC_D4: U1.AE26 (EMMC_D4), U4.A8 (DAT4)
EMMC_D5: U1.AE27 (EMMC_D5), U4.A9 (DAT5)
EMMC_D6: U1.AE28 (EMMC_D6), U4.A10 (DAT6)
EMMC_D7: U1.AF1 (EMMC_D7), U4.A11 (DAT7)
EMMC_RST_N: U1.AF2 (EMMC_RST_N), U4.A3 (RST_N)
EMMC_VDDI: C4.1, U4.B2 (VDDI)
EN_28V: J5.18, U7.58 (PB5)
EN_DRAIN_SW: J4.32, U7.42 (PA8)
EN_HEATER: J5.21, U7.39 (PC7)
EN_NEG5: J5.19, U7.57 (PB4)
EN_RF_5V: J5.20, U7.60 (PB7)
EN_VERSAL: U7.38 (PC6), U20.4 (EN), U21.4 (EN), U22.3 (EN/UV), U23.3 (EN), U24.3 (EN)
FB_3V3: R100.2, R101.1, U22.4 (FB)
FB_U23: R103.2, R104.1, U23.4 (FB)
FB_U24: R105.2, R106.1, U24.4 (FB)
FPGA_REFCLK: J4.23, U1.A25 (GTREFCLK)
FPGA_SYSREF: J4.24, U1.A26 (SYSREF_IN)
GND: C4.2, C7.2, C12.2, C23.2, C24.2, C101.2, C102.2, CL1.2, CL2.2, CR25.2, CR26.2, CR27.2, CR28.2, CR29.2, H1.1, H2.1, H3.1, H4.1, H5.1, H6.1, J2.1, J2.10, J2.11, J2.12, J2.13, J2.14, J2.15, J2.16, J2.17, J2.18, J2.19, J2.21, J2.22, J2.23, J2.25, J2.27, J2.28, J2.29, J2.31, J2.32, J2.33, J2.34, J2.35, J2.36, J2.37, J2.38, J2.39, J2.40, J2.41, J2.42, J2.43, J2.44, J2.45, J2.46, J2.47, J2.48, J2.49, J2.50, J2.51, J2.52, J2.53, J2.54, J2.55, J2.56, J2.57, J2.58, J2.59, J2.60, J2.61, J2.62, J2.63, J2.64, J2.65, J2.66, J2.67, J2.68, J2.69, J2.70, J2.71, J2.72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
GNSS_RF: J4.35, U8.11 (RF_IN)
GNSS_RX: U1.AG1 (GNSS_RX), U8.21 (RXD/SPI_MOSI)
GNSS_TX: U1.AG2 (GNSS_TX), U8.20 (TXD/SPI_MISO)
I2C3_SCL: J4.33, U1.AF27 (PMB_SCL), U7.40 (PC8), U20.5 (PMB_CLK), U21.5 (PMB_CLK)
I2C3_SDA: J4.34, U1.AF28 (PMB_SDA), U7.41 (PC9), U20.6 (PMB_DATA), U21.6 (PMB_DATA)
ID_PA1: J3.5, J3.23, J3.35, J3.47, U7.9 (PC1)
ID_PA2: J3.11, J3.25, J3.37, J3.49, U7.10 (PC2)
ID_PA3: J3.15, J3.27, J3.39, J3.51, U7.11 (PC3)
ID_PA4: J3.17, J3.29, J3.41, J3.53, U7.36 (PB14)
ID_PA5: J3.19, J3.31, J3.43, J3.55, U7.5 (PF0)
ID_PA6: J3.21, J3.33, J3.45, J3.57, U7.34 (PB12)
IMU_CS: U1.AG7 (IMU_CS), U11.12 (CS)
IMU_INT: U1.AG9 (IMU_INT), U11.4 (INT1)
IMU_MISO: U1.AG6 (IMU_MISO), U11.1 (SDO/SA0)
IMU_MOSI: U1.AG5 (IMU_MOSI), U11.14 (SDA), U12.4 (SDA/SDI/SDO)
IMU_SCLK: U1.AG4 (IMU_SCLK), U11.13 (SCL), U12.1 (SCL/SPC)
INTVCC_3V3: C101.1, U22.14 (INTVCC)
JESD1_L0: J2.100, U1.A1 (GTYP_RX_1_0)
JESD1_L1: J2.98, U1.A2 (GTYP_RX_1_1)
JESD1_L2: J2.96, U1.A3 (GTYP_RX_1_2)
JESD1_L3: J2.92, U1.A4 (GTYP_RX_1_3)
JESD2_L0: J2.30, U1.A5 (GTYP_RX_2_0)
JESD2_L1: J2.26, U1.A6 (GTYP_RX_2_1)
JESD2_L2: J2.24, U1.A7 (GTYP_RX_2_2)
JESD2_L3: J2.20, U1.A8 (GTYP_RX_2_3)
JESD3_L0: J2.8, U1.A9 (GTYP_RX_3_0)
JESD3_L1: J2.6, U1.A10 (GTYP_RX_3_1)
JESD3_L2: J2.4, U1.A11 (GTYP_RX_3_2)
JESD3_L3: J2.2, U1.A12 (GTYP_RX_3_3)
JESD4_L0: J3.100, U1.A13 (GTYP_RX_4_0)
JESD4_L1: J3.98, U1.A14 (GTYP_RX_4_1)
JESD4_L2: J3.96, U1.A15 (GTYP_RX_4_2)
JESD4_L3: J3.94, U1.A16 (GTYP_RX_4_3)
JESD5_L0: J3.86, U1.A17 (GTYP_RX_5_0)
JESD5_L1: J3.82, U1.A18 (GTYP_RX_5_1)
JESD5_L2: J3.80, U1.A19 (GTYP_RX_5_2)
JESD5_L3: J3.76, U1.A20 (GTYP_RX_5_3)
JESD6_L0: J3.14, U1.A21 (GTYP_RX_6_0)
JESD6_L1: J3.10, U1.A22 (GTYP_RX_6_1)
JESD6_L2: J3.8, U1.A23 (GTYP_RX_6_2)
JESD6_L3: J3.4, U1.A24 (GTYP_RX_6_3)
JESD_SYNC: J4.20, U1.A27 (JESD_SYNC)
JTAG_TCK: J7.2, U1.AG24 (TCK)
JTAG_TDI: J7.4, U1.AG26 (TDI)
JTAG_TDO: J7.5, U1.AG27 (TDO)
JTAG_TMS: J7.3, U1.AG25 (TMS)
MAG_C1: C12.1, U12.5 (C1)
MAG_CS: U1.AG8 (MAG_CS), U12.3 (~CS)
MCU_SPI_MISO: J4.27, U7.20 (PA6)
MCU_SPI_MOSI: J4.26, U7.21 (PA7)
MCU_SPI_SCK: J4.25, U7.19 (PA5)
MDC: U1.AF15 (MDC), U6.13 (MDC)
MDIO: U1.AF24 (MDIO), U6.14 (MDIO)
NEG_PGOOD: RPG100.2, U7.54 (PC12), U30.1 (OUTA), U30.6 (OUTB)
NRST: C7.1, J8.4, U7.7 (PG10)
NTC_HOUSING: RP1.2, RT1.1, U7.33 (PB11)
NTC_RFIC: RP2.2, RT2.1, U7.24 (PB0)
PHY_INT_N: U1.AF23 (PHY_INT_N), U6.16 (INT_N)
PHY_MD1: J5.1, U6.17 (TD_A+)
PHY_MD2: J5.2, U6.18 (TD_A-)
PHY_MD3: J5.4, U6.19 (TD_B+)
PHY_MD4: J5.5, U6.20 (TD_B-)
PHY_MD5: J5.7, U6.21 (TD_C+)
PHY_MD6: J5.8, U6.22 (TD_C-)
PHY_MD7: J5.10, U6.23 (TD_D+)
PHY_MD8: J5.11, U6.24 (TD_D-)
PHY_RST_N: U1.AF16 (PHY_RST_N), U6.15 (RESET_N)
PHY_XI: U6.26 (XI), Y3.3 (OUT)
PLL_LD_LO: J4.22, U1.AA21 (PLL_LD_LO), U7.53 (PC11)
PLL_LD_TX: J4.21, U1.AA20 (PLL_LD_TX), U7.52 (PC10)
POR_B: RPOR100.2, U1.AG28 (POR_B), U20.23 (PGOOD), U21.23 (PGOOD)
PPS: U1.AG3 (PPS), U8.3 (TIMEPULSE)
PPS_EXT: J5.16, U1.AG21 (PPS_EXT)
PS_REFCLK: U1.AH1 (PS_REFCLK), Y2.3 (OUT)
QSPI_CLK: U1.AF3 (QSPI_CLK), U5.6 (C)
QSPI_CS_N: U1.AF4 (QSPI_CS_N), U5.1 (~S)
QSPI_DQ0: U1.AF5 (QSPI_DQ0), U5.5 (DQ0)
QSPI_DQ1: U1.AF6 (QSPI_DQ1), U5.2 (DQ1)
QSPI_DQ2: U1.AF7 (QSPI_DQ2), U5.3 (~W/DQ2)
QSPI_DQ3: U1.AF8 (QSPI_DQ3), U5.7 (~RESET/DQ3)
REF_U25: CR25.1, U25.8 (REF)
REF_U26: CR26.1, U26.8 (REF)
REF_U27: CR27.1, U27.8 (REF)
REF_U28: CR28.1, U28.8 (REF)
REF_U29: CR29.1, U29.8 (REF)
RF_RESET_N: J4.38, U1.AG23 (RF_RESET_N)
RGMII_RXC: U1.AF17 (RGMII_RXC), U6.7 (RX_CLK)
RGMII_RXD0: U1.AF19 (RGMII_RXD0), U6.9 (RX_D0)
RGMII_RXD1: U1.AF20 (RGMII_RXD1), U6.10 (RX_D1)
RGMII_RXD2: U1.AF21 (RGMII_RXD2), U6.11 (RX_D2)
RGMII_RXD3: U1.AF22 (RGMII_RXD3), U6.12 (RX_D3)
RGMII_RX_CTL: U1.AF18 (RGMII_RX_CTL), U6.8 (RX_CTRL)
RGMII_TXC: U1.AF9 (RGMII_TXC), U6.1 (TX_CLK)
RGMII_TXD0: U1.AF11 (RGMII_TXD0), U6.3 (TX_D0)
RGMII_TXD1: U1.AF12 (RGMII_TXD1), U6.4 (TX_D1)
RGMII_TXD2: U1.AF13 (RGMII_TXD2), U6.5 (TX_D2)
RGMII_TXD3: U1.AF14 (RGMII_TXD3), U6.6 (TX_D3)
RGMII_TX_CTL: U1.AF10 (RGMII_TX_CTL), U6.2 (TX_CTRL)
RID_RF: J4.36, U10.20 (RF)
RS485_DE: J5.15, U1.AG20 (RS485_DE)
RS485_RX: J5.14, U1.AG19 (RS485_RX)
RS485_TX: J5.13, U1.AG18 (RS485_TX)
RT_3V3: R102.1, U22.5 (RT)
SPI_MOSI: J4.3, U1.AA1 (SPI_MOSI)
SPI_SCLK: J4.1, U1.A28 (SPI_SCLK)
SWCLK: J8.3, U7.50 (PA14)
SWDIO: J8.2, U7.49 (PA13)
SW_3V3: C100.2, L3.1, U22.10 (SW), U22.11 (SW)
SW_AIE: L2.1, U21.20 (SW), U21.21 (SW), U21.22 (SW)
SW_U23: L23.1, U23.9 (SW), U23.10 (SW)
SW_U24: L24.1, U24.9 (SW), U24.10 (SW)
SW_VCCINT: L1.1, U20.20 (SW), U20.21 (SW), U20.22 (SW)
TX_LOAD: J4.31, U1.AA19 (TX_LOAD)
TX_MUTE_N: J4.30, U7.59 (PB6)
UART_M2V: U1.AF26 (UART_MCU_RX), U7.43 (PA9)
UART_V2M: U1.AF25 (UART_MCU_TX), U7.44 (PA10)
V3V3_SENSE: RD1.2, RD2.1, U7.17 (PA3)
V5_SENSE: J5.24, U7.14 (PA2)
V28_SENSE: J5.23, U7.13 (PA1)
VCCINT_0V8: CL1.1, L1.2, U1.AH2 (VCCINT), U20.7 (VOSNS+)
VCC_AIE_0V8: CL2.1, L2.2, U1.AH3 (VCC_AIE), U21.7 (VOSNS+)
VIN_SENSE: J5.22, U7.12 (PA0)
VNEG_SENSE: RN1.2, RN2.1, U7.8 (PC0), U7.25 (PB1), U30.3 (INA+), U30.4 (INB-)
WIFI_CS: U1.AG15 (WIFI_CS), U10.4 (SPI_CS)
WIFI_EN: U1.AG17 (WIFI_EN), U10.6 (BUCKEN), U10.7 (IOVDD_EN)
WIFI_IRQ: U1.AG16 (WIFI_IRQ), U10.5 (HOST_IRQ)
WIFI_MISO: U1.AG14 (WIFI_MISO), U10.3 (SPI_MISO)
WIFI_MOSI: U1.AG13 (WIFI_MOSI), U10.2 (SPI_MOSI)
WIFI_SCK: U1.AG12 (WIFI_SCK), U10.1 (SPI_SCK)

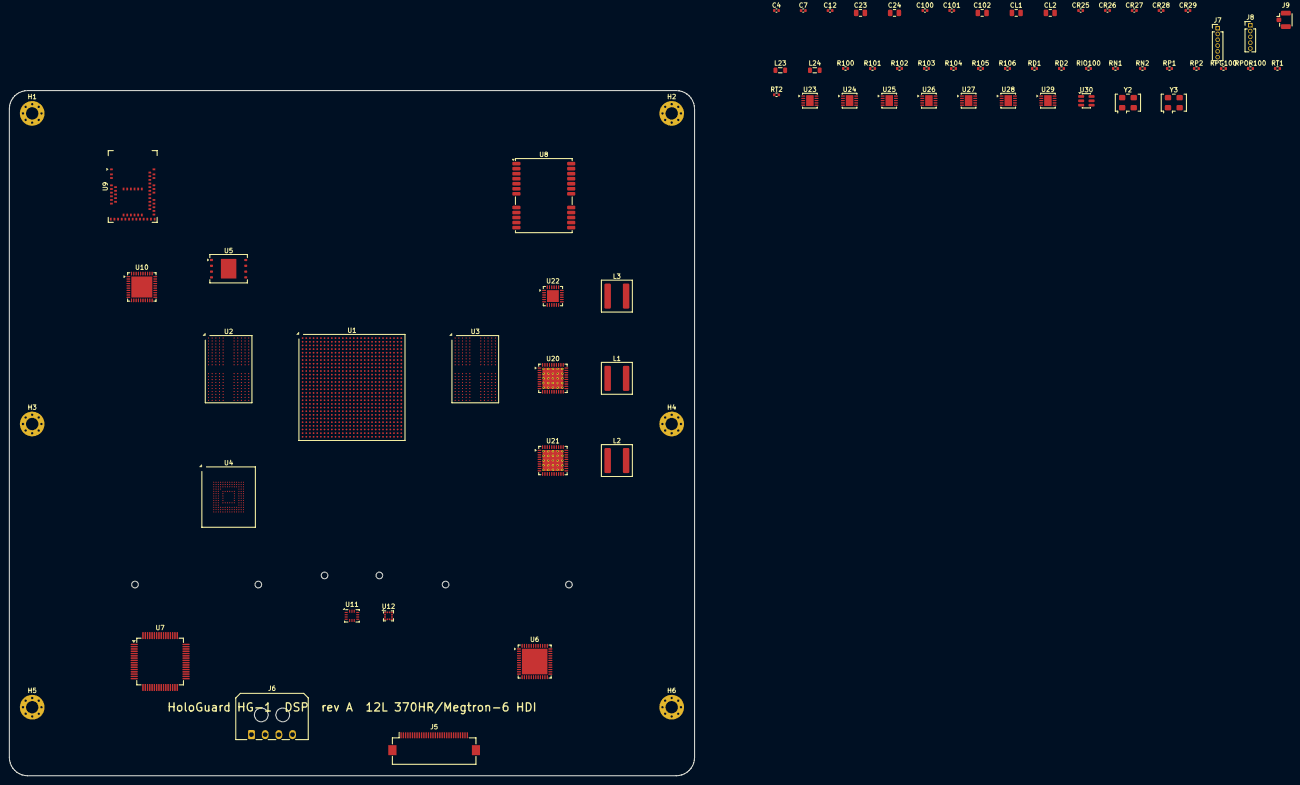
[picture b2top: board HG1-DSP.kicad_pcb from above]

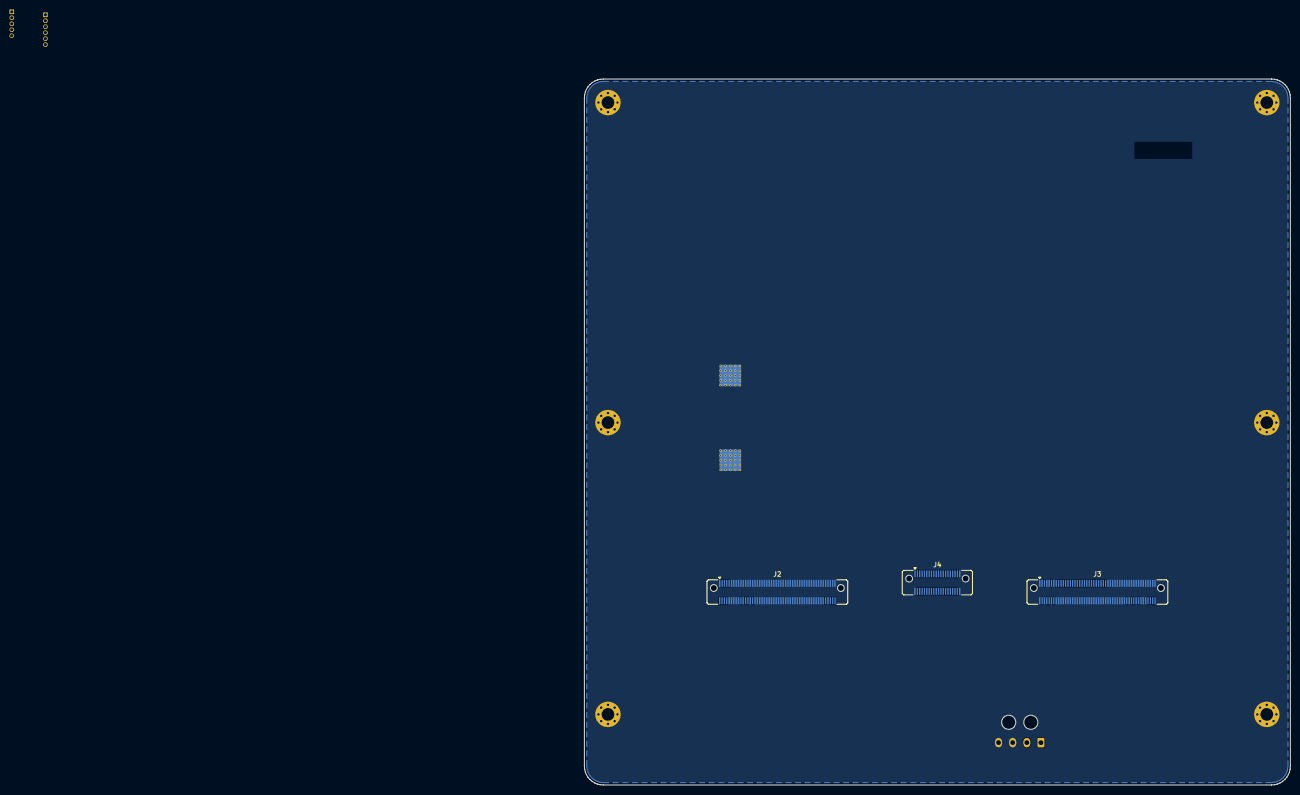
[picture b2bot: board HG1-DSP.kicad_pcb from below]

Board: 12 copper layers, 150.0 x 150.0 mm, 77 parts (3 on the bottom side), 297 nets, no tracks yet.
